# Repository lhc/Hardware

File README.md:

# Desenvolvimento de HW LHC
Desde a sua fundação vários projetos de HW Hardware abertos foram desenvolvidos no LHC, usando diferentes processadores e ferramentas. Este repositório contém todos os projetos já desenvolvidos no LHC.

# Contribua e participe dos projetos com Hardware no LHC
Acesse o nosso forms e se conecte ao time do Laboratório Hacker de Campinas, através da criação de sua conta no forum e conversando com o pessoal sobre os diversos projetos. [https://discourse.lhc.net.br](https://discourse.lhc.net.br/c/hardware/21)

# Projetos
 2024
- [LHCbit](https://github.com/lhc/Hardware/tree/main/LHCbit)
- 
- [Venda limitada, pegue a sua placa antes que acabe](https://forms.gle/h3qhtFoRbykofKP68)
- [Construindo sua placa em KICAD](https://github.com/lhc/Hardware/tree/main/Oficinas/monte-sua-placa-kicad)
- [nodeLHC](https://github.com/lhc/Hardware/tree/main/nodeLHC)
- [nodeLHC-ESP32](https://github.com/lhc/Hardware/tree/main/nodeLHC-ESP32)

# Oficinas
- [Evento: Construindo sua placa em KiCad](https://github.com/lhc/Hardware/tree/main/Oficinas/monte-sua-placa-kicad)

# Portes
- [Porte da LHCbit para NuttX](https://github.com/apache/nuttx/blob/master/Documentation/platforms/xtensa/esp32s3/boards/esp32s3-lhcbit/index.rst)

# Bibliotecas
- [KiCad LHC](https://github.com/lhc/Hardware/tree/main/Libraries/lhc_kicad_library)

# Contribuidores
- Leandro Pereira
- Douglas Esteves
- Jorge Guzman
- Manassés Souza
- Marcelo Junqueira
- Matheus Brito
- Estevan
- Pedro Minatel
- Rafael Estevam
- Alexandre Fernandes
- Rodrigo Azevedo
- Gustavo Ortenzi

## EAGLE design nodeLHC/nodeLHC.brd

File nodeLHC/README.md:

# nodeLHC
nodeLHC

This board was developed at the Campinas Hacker Lab in Brazil during our weekly IoT meetings. This layout and schematic was developed by Leandro Pereira.

The idea was to develop a easy to use board and to learn how to use this magnificent WiFi module.

We are not selling it but you can build your own borad if you want!!!

This board is full compatible with nodeMCU, Arduino IDE, native development and any other firmware avaliable.

#Link nodeLHC
https://lhc.net.br/wiki/NodeLHC

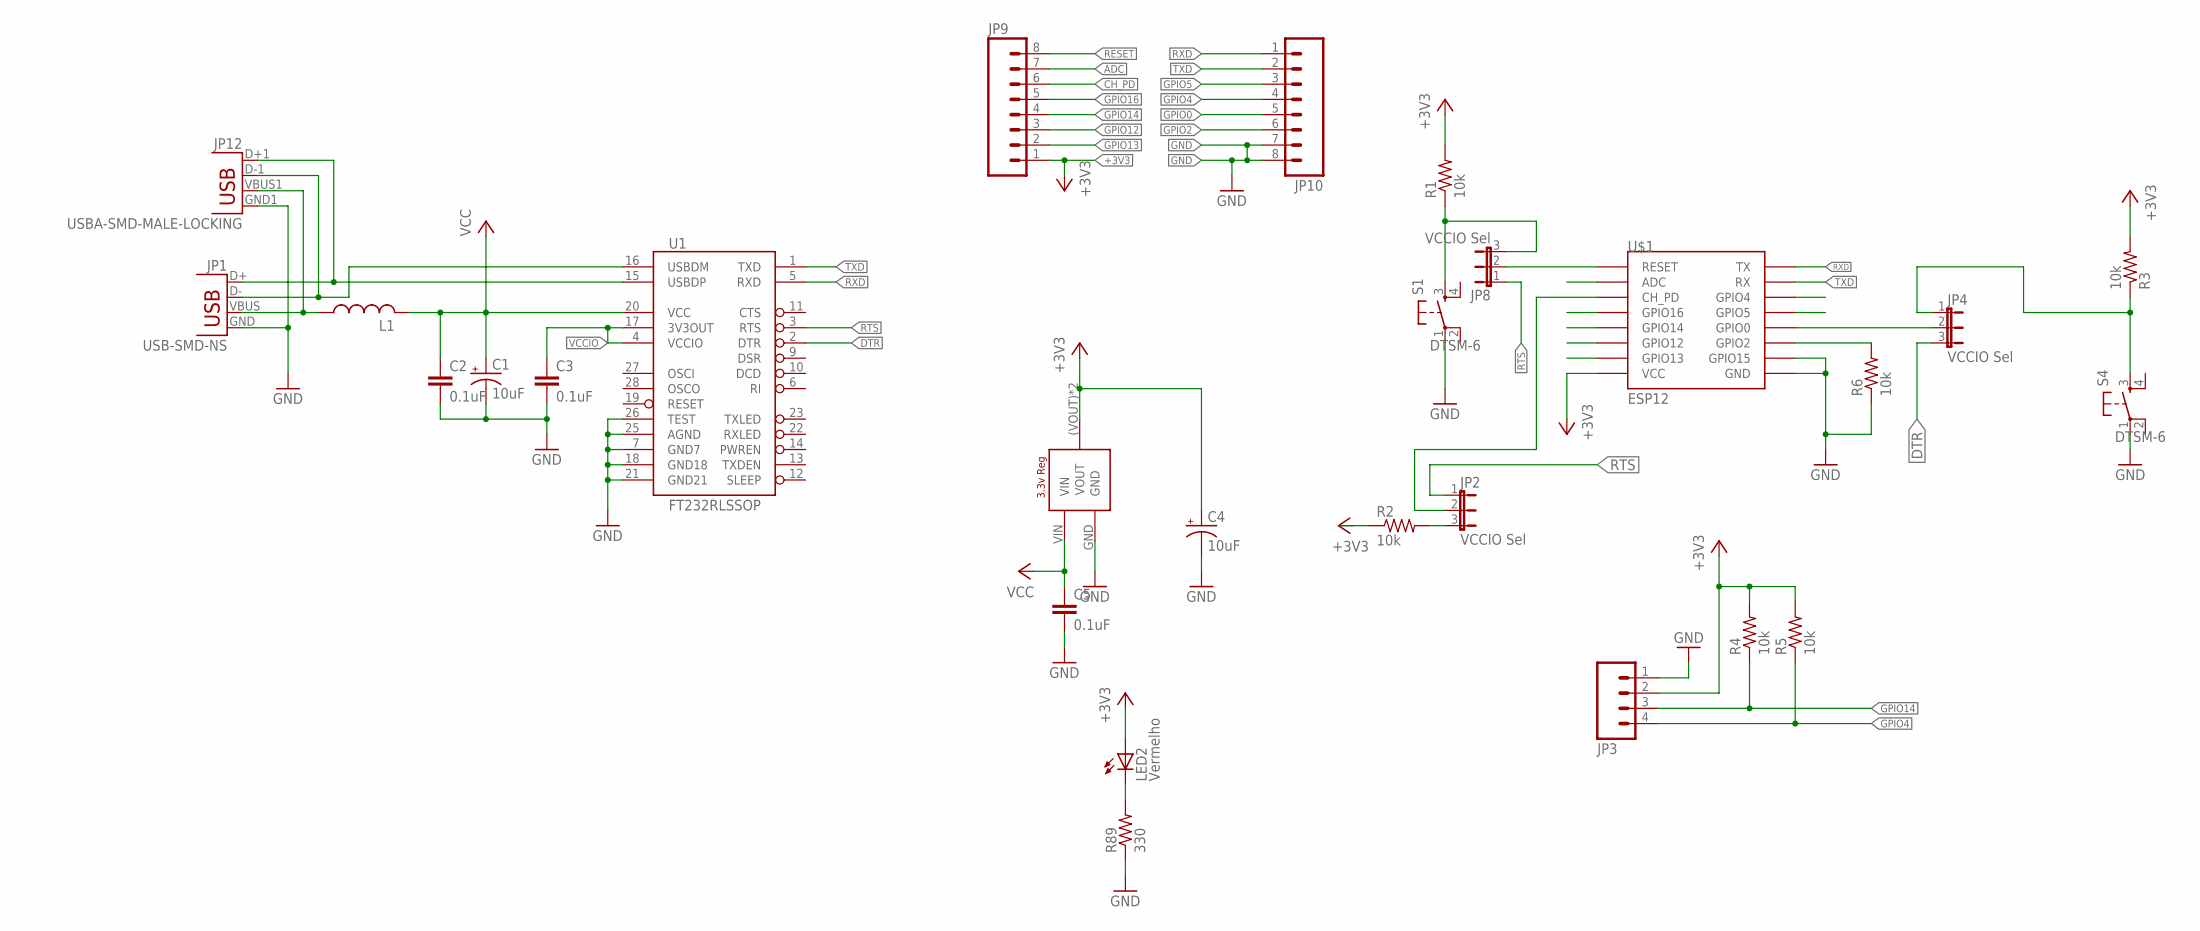
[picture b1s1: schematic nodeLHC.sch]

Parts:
C1, C4: 10uF; 153CLV-0505
C2, C3, C5: 0.1uF; C0603K
JP1: USB-SMD-NS; USB-MINIB-NOSTOP
JP2, JP4, JP8: VCCIO Sel; SJ_3
JP3: M04PTH; 1X04
JP9, JP10: M08; 1X08_ROUND
JP12: USBA-SMD-MALE-LOCKING; USB-A-SMT-MALE-LOCKING
L1: L-US; C0603K
LED2: Vermelho; CHIP-LED0805
R1, R2, R3, R4, R5, R6: 10k; R0603
R89: 330; R0603
S1, S4: DTSM-6
U1: FT232RLSSOP; SSOP28DB
U$1: ESP12
U$2: LD1117; LD1117SOT-223

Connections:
+3V3: C4.+, JP3.2, JP9.1, LED2.A, R1.2, R2.1, R3.2, R4.2, R5.2, U$1.VCC, U$2.(VOUT) (VOUT), U$2.VOUT
ADC: JP9.7, U$1.ADC
CH_PD: JP2.2, JP9.6, U$1.CH_PD
DTR: JP4.3, U1.2 (DTR)
GND: C1.-, C2.2, C3.2, C4.-, C5.2, JP1.GND, JP3.1, JP10.7, JP10.8, JP12.GND1 (GND), R6.1, R89.1, S1.1, S4.1, U1.7 (GND7), U1.18 (GND18), U1.21 (GND21), U1.25 (AGND), U1.26 (TEST), U$1.GND, U$1.GPIO15, U$2.GND
GPIO0: JP4.2, JP10.5, U$1.GPIO0
GPIO2: JP10.6, R6.2, U$1.GPIO2
GPIO4: JP3.4, JP10.4, R5.1, U$1.GPIO5
GPIO5: JP10.3, U$1.GPIO4
GPIO12: JP9.3, U$1.GPIO12
GPIO13: JP9.2, U$1.GPIO13
GPIO14: JP3.3, JP9.4, R4.1, U$1.GPIO14
GPIO16: JP9.5, U$1.GPIO16
unnamed: JP2.3, R2.2
unnamed: JP4.1, R3.1, S4.3
unnamed: JP1.VBUS, JP12.VBUS1 (VBUS), L1.1
unnamed: JP1.D+, JP12.D+1 (D+), U1.15 (USBDP)
unnamed: JP1.D-, JP12.D-1 (D-), U1.16 (USBDM)
unnamed: LED2.C, R89.2
RESET: JP8.2, JP9.8, U$1.RESET
RST: JP8.3, R1.1, S1.3
RTS: JP2.1, JP8.1, U1.3 (RTS)
RXD: JP10.1, U1.5 (RXD), U$1.TX
TXD: JP10.2, U1.1 (TXD), U$1.RX
VCC: C1.+, C2.1, C5.1, L1.2, U1.20 (VCC), U$2.VIN
VCCIO: C3.1, U1.4 (VCCIO), U1.17 (3V3OUT)

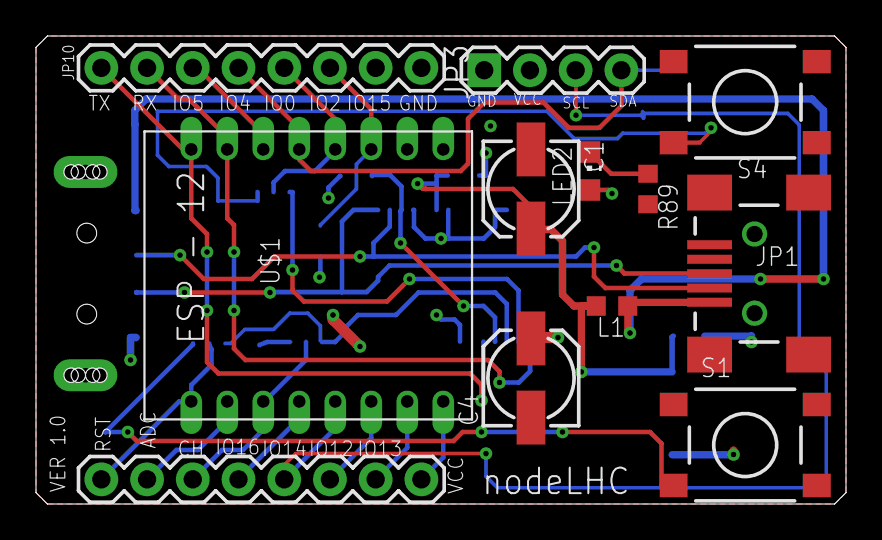
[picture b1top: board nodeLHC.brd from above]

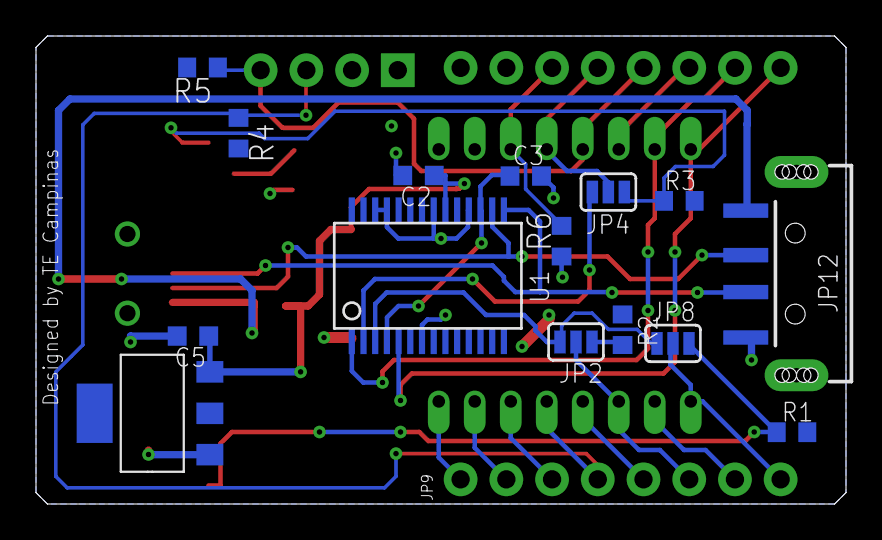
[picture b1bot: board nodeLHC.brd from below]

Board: 2 copper layers, 45.0 x 26.0 mm, 27 parts (15 on the bottom side), 26 nets.

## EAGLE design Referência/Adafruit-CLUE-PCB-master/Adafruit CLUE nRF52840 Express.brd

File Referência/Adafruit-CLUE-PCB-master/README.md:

## Adafruit CLUE nRF52840 Express PCB

<a href="http://www.adafruit.com/products/4500"><br/>
Click here to purchase one from the Adafruit shop</a>

PCB files for the Adafruit CLUE nRF52840 Express. 

Format is EagleCAD schematic and board layout
* https://www.adafruit.com/product/4500

### Description

Do you feel like you just don't have a CLUE? Well, we can help with that - get a CLUE here at Adafruit by picking up this sensor-packed development board. We wanted to build some projects that have a small screen and a lot of sensors. To make it compatible with existing projects, we made it the same shape and size as the BBC micro:bit and with the same edge-connector on the bottom with 5 big pads so it will fit into your existing robot kit or 'bit add-on. This is the alpha release of the hardware.

While the CLUE looks a bit like a 'bit it has totally redesigned-from-scratch technology:

* Nordic nRF52840 Bluetooth LE processor - 1 MB of Flash, 256KB RAM, 64 MHz Cortex M4 processor
* 1.3″ 240×240 Color IPS TFT display for high resolution text and graphics
* Power it from any 3-6V battery source (internal regulator and protection diodes)
* Two A / B user buttons and one reset button
* Tons of sensors!
  * ST Micro series 9-DoF motion - LSM6DS33 Accel/Gyro + LIS3MDL magnetometer
  * APDS9960 Proximity, Light, Color, and Gesture Sensor
  * PDM Microphone sound sensor
  * SHT Humidity
  * BMP280 temperature and barometric pressure/altitude
* RGB NeoPixel indicator LED
* 2 MB internal flash storage for datalogging, images, fonts or CircuitPython code
* Buzzer/speaker for playing tones and beeps
* Two bright white LEDs in front for illumination / color sensing.
* Qwiic / STEMMA QT connector for adding more sensors, motor controllers, or displays over I2C. You can plug in GROVE I2C sensors by using an adapter cable.
* Programmable with Arduino IDE or CircuitPython

Please note that at this time there is no MakeCode or Scratch support for the nRF52840 chipset (of course, we’d love to see MakeCode but there is no ETA when it may be added). While the CLUE is the same outline and we did our best to make the edge-connector pins match up, most cases for the 'bit wont fit the CLUE, and code may not be immediately compatible without adjustment, especially since only Arduino and CircuitPython are supported at this time.

The CLUE is designed for projects that use a ton of sensors - and they're all built in! So you can start exploring your world, measuring, logging and learning. You can transmit data over Bluetooth to a computer or mobile device for data plotting and logging, or save it to the built in storage.

### License

Adafruit invests time and resources providing this open source design, please support Adafruit and open-source hardware by purchasing products from [Adafruit](https://www.adafruit.com)!

Designed by Limor Fried/Ladyada for Adafruit Industries.

Creative Commons Attribution/Share-Alike, all text above must be included in any redistribution. 
See license.txt for additional details.

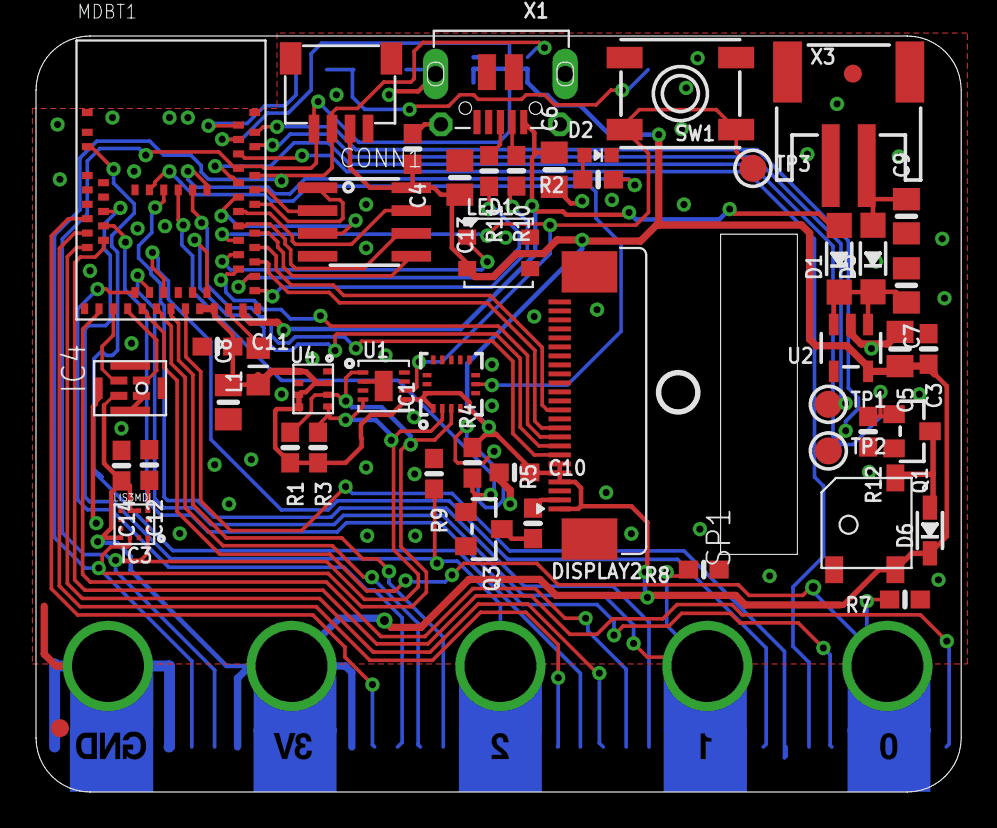
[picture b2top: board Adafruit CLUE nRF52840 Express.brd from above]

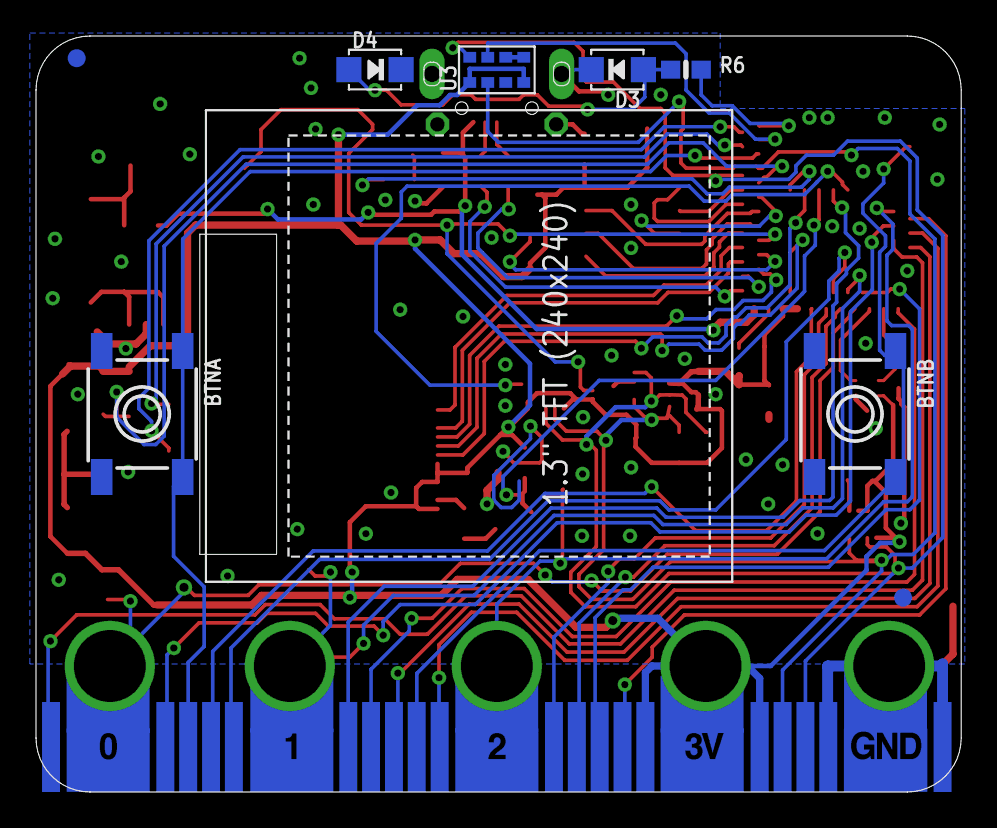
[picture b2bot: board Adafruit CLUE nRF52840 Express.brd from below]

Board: 2 copper layers, 51.4 x 42.0 mm, 62 parts (10 on the bottom side), 59 nets.

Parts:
BTNA: 6mm; 6MMX6MM_TACTILE_SMT
BTNB: 6mm; 6MMX6MM_TACTILE_SMT
C3, C4, C10, C11, C12, C14: 0.1uF; 0603-NO
C5, C6, C7, C8, C9, C13: 10uF; 0805-NO
CONN1: STEMMA_I2C_QT; JST_SH4
D1, D5: MBR120; SOD-123
D2: RED; CHIPLED_0603_NOOUTLINE
D3, D4: L130-5780001400001; EVERLIGHT_45-21
D6: 1N4148; SOD-323
DISPLAY2: DISP_LCD_ST7789_1.3IN; TFT_1.3IN_240X240_24P
FID1, FID2, FID3, FID4: FIDUCIAL_1MM
IC1: LSM6DS33; LGA16_3X3MM
IC2: GD25Q16; SOIC8_150MIL
IC3: LIS3MDL; LGA12_2X2MM
IC4: MIC_PDM; SPK0415HM4H
L1: DNP; _0805MP
LED1: WS2812B3535; LED3535
MB1: MICRO:BIT_EDGE; MICROBIT_EDGE
MDBT1: MDBT50
Q1, Q3: BSS138; SOT23-WIDE
R1, R3: 4.7K; 0603-NO
R2: 1K; 0603-NO
R4, R12: 10K; 0603-NO
R5, R6: 10; 0603-NO
R7, R8, R9: 1Mohm; 0603-NO
R10, R11: 22; 0603-NO
SP1: SPEAKER_BUZZER5MM; BUZZER_SMT_5MM
SW1: KMR2; EVQ-Q2_SMALLER
TP1, TP2, TP3: TESTPOINT_ROUND_1.5MM
U1: SHT30; SHT3X
U2: AP2112(3.3V); SOT23-5
U3: APDS-9960
U4: BMP280
U$10: PCBFEAT-REV-056
U$37: CLUE_BACK
U$52: CLUE_FRONT
X1: 4u20329; 4UCONN_20329_SLIM
X3: JSTPH; JSTPH2

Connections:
3.3V: C3.2, C4.2, C5.2, C8.2, C10.2, C11.2, C13.2, C14.2, CONN1.2, D6.C, DISPLAY2.1, DISPLAY2.4, DISPLAY2.5, DISPLAY2.6, IC1.1, IC1.5, IC1.16, IC2.8, IC3.5, IC3.6, IC3.10, IC4.1, L1.1, LED1.2, MB1.+3V3, MB1.+3V3@1, MB1.+3V3@2, MDBT1.28, MDBT1.30, R1.2, R3.2, R4.2, SP1.+, U1.5, U2.5, U3.5, U3.8, U4.2, U4.5, U4.6, U4.8
APDS_IRQ: MDBT1.52, U3.2
BACKLIGHT: MDBT1.59, Q3.1, R4.1
CAP1: C12.2, IC3.4
D0/AIN2: MB1.P0, MDBT1.20, R7.2
D1/AIN3: MB1.P1, MDBT1.21, R8.2
D2/AIN4: MB1.P2, MDBT1.9, R9.2
D3/AIN5: MB1.P3, MDBT1.13
D4/AIN6: MB1.P4, MDBT1.11
D5/BUTTON_A: BTNA.B, BTNA.B', MB1.P5, MDBT1.50
D6: MB1.P6, MDBT1.26
D7: MB1.P7, MDBT1.23
D8: MB1.P8, MDBT1.58
D9: MB1.P9, MDBT1.16
D10/AIN7: MB1.P10, MDBT1.14
D11/BUTTON_B: BTNB.B, BTNB.B', MB1.P11, MDBT1.3
D12/AIN0: MB1.P12, MDBT1.12
D13/SCK: MB1.P13, MDBT1.24
D14/MISO: MB1.P14, MDBT1.22
D15/MOSI: MB1.P15, MDBT1.19
D16/AIN1: MB1.P16, MDBT1.10
D19/SCL: CONN1.4, IC1.2, IC3.1, MB1.P19, MDBT1.49, R3.1, U1.4, U3.7, U4.4
D20/SDA: CONN1.3, IC1.3, IC3.11, MB1.P20, MDBT1.48, R1.1, U1.1, U3.1, U4.3
D+: R11.1, X1.D+
D-: R10.1, X1.D-
DCCH: L1.2, MDBT1.31
GND: BTNA.A, BTNA.A', BTNB.A, BTNB.A', C3.1, C4.1, C5.1, C6.1, C7.1, C8.1, C9.1, C10.1, C11.1, C12.1, C13.1, C14.1, CONN1.1, CONN1.MT1, CONN1.MT2, D2.C, D3.K, D4.K, DISPLAY2.3, DISPLAY2.11, DISPLAY2.13, DISPLAY2.14, DISPLAY2.15, DISPLAY2.16, DISPLAY2.17, DISPLAY2.18, DISPLAY2.19, DISPLAY2.20, DISPLAY2.23, DISPLAY2.24, IC1.4, IC1.8, IC1.9, IC1.10, IC1.11, IC1.12, IC1.13, IC1.15, IC2.4, IC3.2, IC3.3, IC3.9, IC3.12, IC4.2, IC4.5, IC4.6, IC4.7, IC4.8, LED1.4, MB1.GND, MB1.GND@1, MB1.GND@2, MDBT1.1, MDBT1.2, MDBT1.15, MDBT1.33, MDBT1.55, Q1.2, Q3.2, R7.1, R8.1, R9.1, R12.2, SW1.A, SW1.A', U1.2, U1.7, U1.8, U1.THERMAL, U2.2, U3.6, U4.1, U4.7, X1.BASE@1, X1.BASE@2, X1.GND, X1.SPRT@1, X1.SPRT@2, X1.SPRT@3, X1.SPRT@4, X3.1
LED1: MDBT1.61, R2.1
LEDK: DISPLAY2.2, R5.2
LSM_IRQ: IC1.7, MDBT1.57
unnamed: Q3.3, R5.1
unnamed: U3.3, U3.4
unnamed: D3.A, D4.A, R6.1
unnamed: D6.A, Q1.3, SP1.-
unnamed: D2.A, R2.2
NEOPIX: LED1.1, MDBT1.38
PDM_CLK: IC4.3, MDBT1.18
PDM_DAT: IC4.4, MDBT1.17
QSPI_CS: IC2.1, MDBT1.44
QSPI_DATA0: IC2.5, MDBT1.41
QSPI_DATA1: IC2.2, MDBT1.46
QSPI_DATA2: IC2.3, MDBT1.45
QSPI_DATA3: IC2.7, MDBT1.43
QSPI_SCK: IC2.6, MDBT1.42
RESET: MDBT1.40, SW1.B, SW1.B', TP3.P$1, U1.6
SPKR: MDBT1.47, Q1.1, R12.1
SWCLK: MDBT1.53, TP2.P$1
SWDIO: MDBT1.51, TP1.P$1
TFT_CS: DISPLAY2.8, MDBT1.29
TFT_DC: DISPLAY2.10, MDBT1.37
TFT_MOSI: DISPLAY2.12, MDBT1.39
TFT_RESET: DISPLAY2.7, MDBT1.60
TFT_SCK: DISPLAY2.9, MDBT1.36
USBD+: MDBT1.35, R11.2
USBD-: MDBT1.34, R10.2
VBAT: C9.2, D5.A, X3.2
VBUS: C6.2, D1.A, MDBT1.32, X1.VBUS
VHI: C7.2, D1.C, D5.C, U2.1, U2.3
WHITE_LED: MDBT1.54, R6.2

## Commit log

2023-12-16 Commit inicial
2023-12-17 Mudança para o rak-3172-sip
2023-12-22 Adicionado todos os componentes
2024-02-28 Conclusão do esquemático
2024-02-28 Update do arquivo pcb
2024-02-29 Conclusão do posicionamento dos componentes
2024-04-12 Conclusão do projeto com redução do tamanho do plano de ground
2024-04-15 Correção curto do footprint do conector microbit
2024-04-15 Atualização de BOM com componentes 0402
2024-04-18 Inclusão da BOM
2024-04-19 Ajuste BOM para fabricação
2024-04-19 Ajuste draftsman
2024-04-29 Junção de todos os projetos de HW
2024-05-01 Update README: removendo duplicações e organizando links
2024-06-20 Updated docs LHCbit
2024-07-18 Update README.md: nomes apoiadores
2024-07-19 update README: seção ambiente local
2024-07-19 Update README.md Correção gramatical texto em Pt-br
2024-07-27 add auto-add contributors action
2024-07-27 Update README.md: contributors reference
2024-07-28 docs(README): update contributors
2024-07-28 Update README.md: seção contributors
2024-08-17 separando arquivos altium
2024-08-22 teste da importação dos arquivos altium
2024-08-24 update gitignore
2024-08-27 update README: contributors
2024-08-28 docs(README): update LHCBit contributors
2024-08-30 Fixed display footprint
2024-08-30 Fixed LHCbit display
2024-08-30 Added keepout for usb connector
2024-09-05 Fixed display pinout
    Version 2.0 LHCbit
2024-09-13 Added reset button for LHCbit
2024-10-04 Improved silkscreen of LHCbit
2024-10-09 Versão preliminar da placa LHCbit importada para o Kicad, ainda faltam pequenos ajustes de posicionamento, camadas e correção dos erros de DRC.
2024-10-31 Changed button s2 to IO0 and added header for uart

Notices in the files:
parts and their libraries:
microbuilder: This work is placed in the public domain, and may be freely used for commercial and non-commercial work with the following conditions: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
SparkFun-Connectors: Licensing: Creative Commons ShareAlike 4.0 International - https://creativecommons.org/licenses/by-sa/4.0
